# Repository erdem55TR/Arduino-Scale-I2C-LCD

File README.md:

Arduino-based scale with 10kg capacity and 1gram accuracy.

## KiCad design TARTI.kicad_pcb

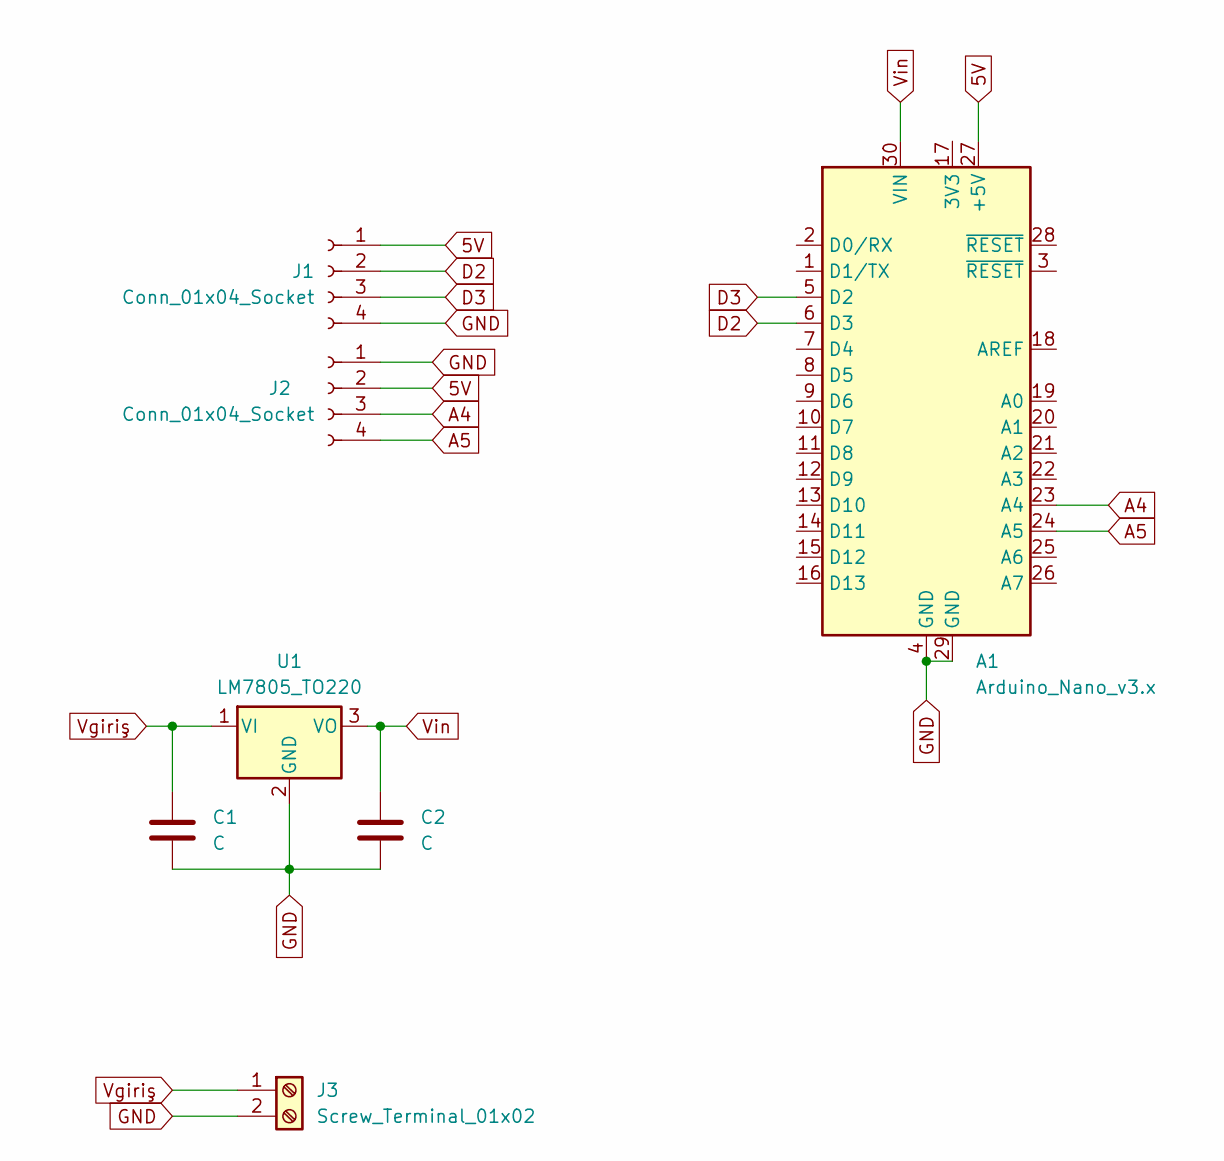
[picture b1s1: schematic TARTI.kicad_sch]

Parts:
A1: Arduino_Nano_v3.x; Arduino_Nano
C1, C2: C; C_Disc_D10.5mm_W5.0mm_P10.00mm
J1, J2: Conn_01x04_Socket; PinSocket_1x04_P2.54mm_Vertical
J3: Screw_Terminal_01x02; PhoenixContact_MCV_1,5_2-G-5.08_1x02_P5.08mm_Vertical
U1: LM7805_TO220; TO-247-3_Vertical

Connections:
5V: A1.27 (+5V), J1.1, J2.2
A4: A1.23 (A4), J2.3
A5: A1.24 (A5), J2.4
D2: A1.6 (D3), J1.2
D3: A1.5 (D2), J1.3
GND: A1.4 (GND), A1.29 (GND), C1.2, C2.2, J1.4, J2.1, J3.2, U1.2 (GND)
Vgiriş: C1.1, J3.1, U1.1 (VI)
Vin: A1.30 (VIN), C2.1, U1.3 (VO)

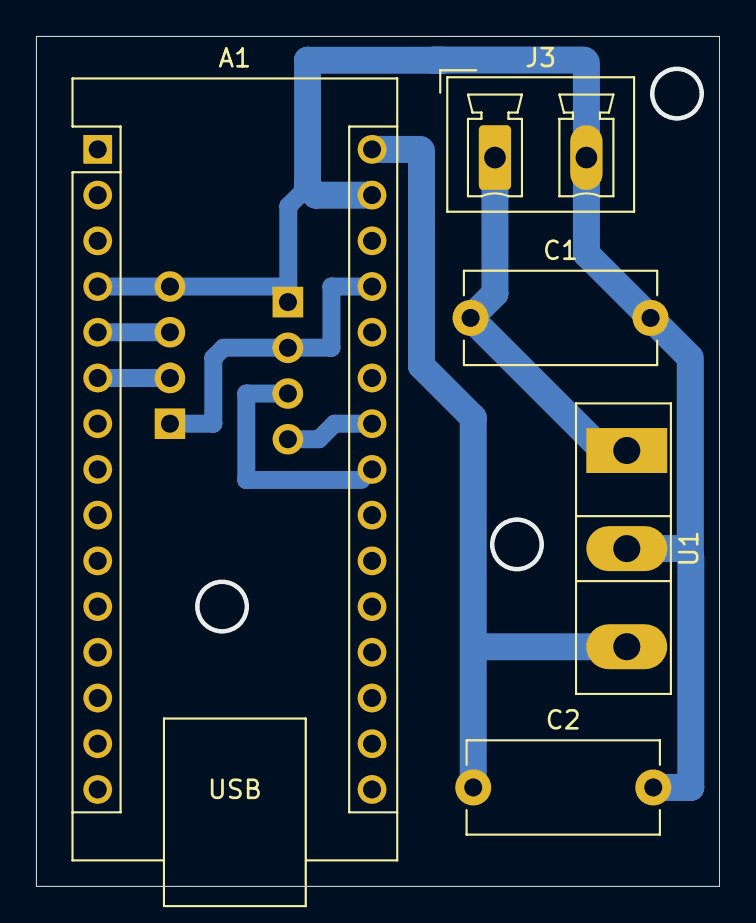
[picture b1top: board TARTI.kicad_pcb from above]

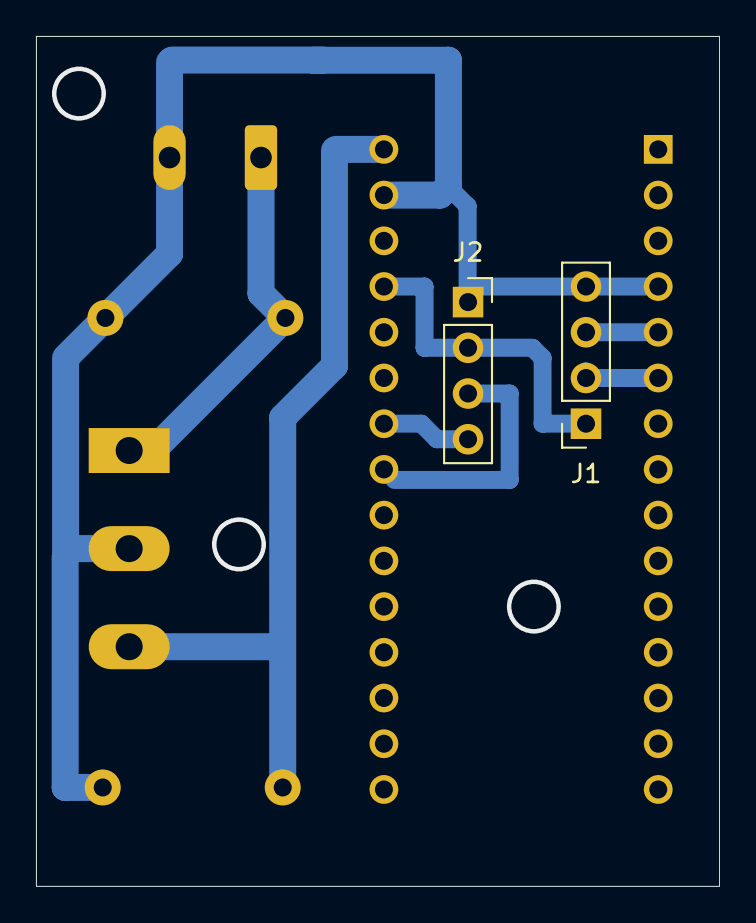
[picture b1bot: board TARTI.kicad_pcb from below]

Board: 2 copper layers, 37.9 x 47.2 mm, 7 parts (2 on the bottom side), 8 nets.
